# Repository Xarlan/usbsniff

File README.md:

# usbsniff
Develop hardware usb 2.0 sniffer

The main idea - to develop cheap hardware usb sniffer which possible to assemble at home :)

Current version based on MAX3421E

/pcb

This folder contain KiCad project of usb sniffer

## Limitation

Support follow EP:
* EP0: CONTROL (64 bytes)
* EP1: OUT, BULK or INTERRUPT
* EP2: IN, BULK or INTERRUPT
* EP3: IN, BULK or INTERRUPT

Thank you for "x8-999-github" for some good advices and idea.

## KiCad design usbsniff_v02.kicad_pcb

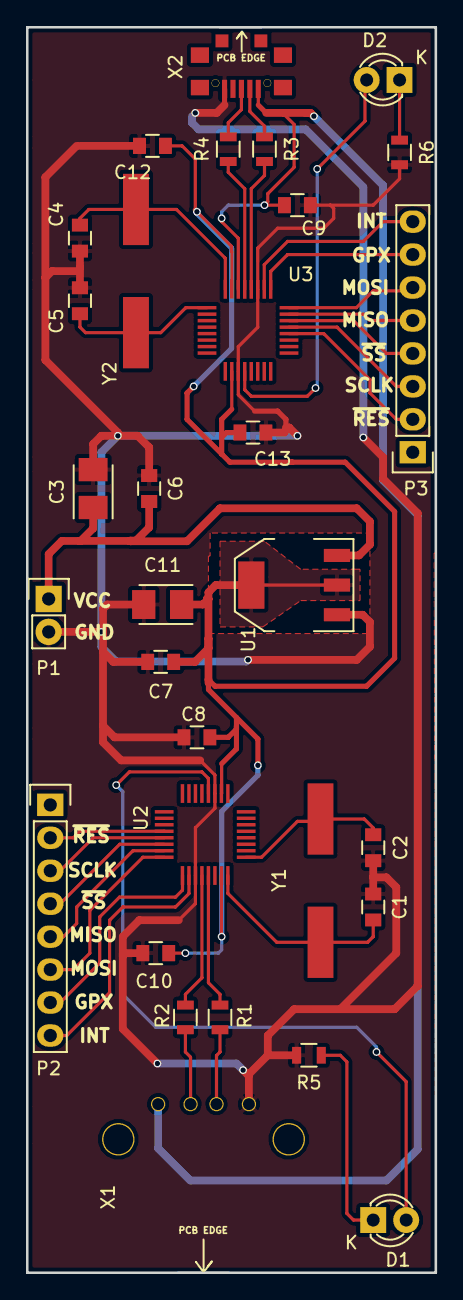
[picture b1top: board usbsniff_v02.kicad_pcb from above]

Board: 2 copper layers, 31.5 x 96.0 mm, 31 parts (0 on the bottom side), 34 nets.

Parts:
C1, C2, C4, C5: 20pF; C_0805
C3, C11: 10uF; TantalC_SizeB_EIA-3528_Reflow
C6, C7, C8, C13: 0.1uF; C_0805
C9, C10, C12: 1uF; C_0805
D1, D2: LED; LED-3MM
P1: CONN_01X02; Pin_Header_Straight_1x02
P2, P3: CONN_01X08; Pin_Header_Straight_1x08
R1, R2, R3, R4: 33 Ohm; R_0805
R5, R6: 470 Ohm; R_0805
U1: AMS1117; SOT-223
U2, U3: MAX3421E; TQFP-32_5x5mm
X1: USB_type_A; USBA_1J_DS_1095_WR
X2: micro_USB; micro_USB_KLS1-233-0-0-1-T
Y1, Y2: 12MHz; HC49-SM

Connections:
/RES_edevice: P3.2, U3.12
/RES_ehost: P2.2, U2.12
/Vcc_3.3V: C7.1, C8.1, C10.2, C11.1, C12.2, C13.1, U1.2, U1.4, U2.2, U2.23, U3.2, U3.23
/XI_device: C4.1, U3.24, Y2.1
/XI_host: C1.1, U2.24, Y1.1
/XO_device: C5.1, U3.25, Y2.2
/XO_host: C2.1, U2.25, Y1.2
/ed_VBCOMP: C9.1, U3.22, X1.1, X2.1
/edevice_DM: R3.2, U3.20
/edevice_DP: R4.2, U3.21
/ehost_DM: R2.1, U2.20
/ehost_DP: R1.1, U2.21
GND: C1.2, C2.2, C3.2, C4.2, C5.2, C6.2, C7.2, C8.2, C9.2, C10.1, C11.2, C12.1, C13.2, P1.2, R5.2, R6.2, U1.1, U2.3, U2.19, U3.3, U3.19, X1.4, X2.5
unnamed: C3.1, C6.1, P1.1, U1.3
unnamed: D1.1, R5.1
unnamed: D1.2, U2.4
unnamed: D2.1, R6.1
unnamed: D2.2, U3.4
unnamed: P2.3, U2.13
unnamed: P2.4, U2.14
unnamed: P2.5, U2.15
unnamed: P2.6, U2.16
unnamed: P2.7, U2.17
unnamed: P2.8, U2.18
unnamed: P3.3, U3.13
unnamed: P3.4, U3.14
unnamed: P3.5, U3.15
unnamed: P3.6, U3.16
unnamed: P3.7, U3.17
unnamed: P3.8, U3.18
unnamed: R1.2, X1.3
unnamed: R2.2, X1.2
unnamed: R3.1, X2.2
unnamed: R4.1, X2.3

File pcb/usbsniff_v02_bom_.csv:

Component,Description,Part,References,Value,Footprint,Quantity Per PCB,Datasheet
1,Unpolarized capacitor,C_Small,C6 C7 C8 C13,0.1uF,C_0805,4,
2,Polarised capacitor,CP_Small,C3 C11,10uF,TantalC_SizeB_EIA-3528_Reflow,2,
3,Unpolarized capacitor,C_Small,C9 C10 C12,1uF,C_0805,3,
4,Unpolarized capacitor,C_Small,C1 C2 C4 C5,20pF,C_0805,4,
5,,LED,D1 D2,LED,LED-3MM,2,
6,Connector 01x02,CONN_01X02,P1,CONN_01X02,Pin_Header_Straight_1x02,1,
7,Connector 01x08,CONN_01X08,P2 P3,CONN_01X08,Pin_Header_Straight_1x08,2,
8,Resistor,R_Small,R1 R2 R3 R4,33 Ohm,R_0805,4,
9,Resistor,R,R5 R6,470 Ohm,R_0805,2,
10,Adjustable/Fixed Low Dropout Linear Regulator,AMS1117,U1,AMS1117,SOT-223,1,
11,USB Peripheral/Host Controller with SPI Interface,MAX3421E,U2 U3,MAX3421E,TQFP-32_5x5mm,2,
12,"socket USB type A, horizontal placement",USB_type_A,X1,USB_type_A,USBA_1J_DS_1095_WR,1,
13,,micro_USB,X2,micro_USB,micro_USB_KLS1-233-0-0-1-T,1,
14,Two pin crystal,Crystal_Small,Y1 Y2,12MHz,HC49-SM,2,





Component Groups:,14
Component Count:,31
Fitted Components:,31
Number of PCBs:,1
Total components:,31
Schematic Version:,
Schematic Date:,
BoM Date:,Wed 21 Mar 2018 09:01:28 PM MSK
Schematic Source:,/home/xarlan/git/usbsniff/usbsniff_v02.sch
KiCad Version:,Eeschema 4.0.2+dfsg1-stable

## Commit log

2018-03-14 have done schematic and pcb based on MAX3421
2018-03-14 add picture of prototype
2018-03-21 add LED, redesign pcb
2018-03-22 redesign wires
2018-03-23 fix polygon around ams1117
2018-05-09 Create software
2018-05-09 Rename bom.ini to pcb/bom.ini
2018-05-09 Rename usbsniff_v02-cache.lib to pcb/usbsniff_v02-cache.lib
2018-05-09 Rename usbsniff_v02.bak to pcb/usbsniff_v02.bak
2018-05-09 Rename usbsniff_v02.kicad_pcb to pcb/usbsniff_v02.kicad_pcb
2018-05-09 Rename usbsniff_v02.kicad_pcb-bak to pcb/usbsniff_v02.kicad_pcb-bak
2018-05-09 Rename usbsniff_v02.net to pcb/usbsniff_v02.net
2018-05-09 Rename usbsniff_v02.pro to pcb/usbsniff_v02.pro
2018-05-09 Rename usbsniff_v02.sch to pcb/usbsniff_v02.sch
2018-05-09 Rename usbsniff_v02.xml to pcb/usbsniff_v02.xml
2018-05-09 Rename usbsniff_v02_add.net to pcb/usbsniff_v02_add.net
2018-05-09 Rename usbsniff_v02_bom_.csv to pcb/usbsniff_v02_bom_.csv
2018-05-09 Rename usbsniff_v02_max.net to pcb/usbsniff_v02_max.net
2018-05-09 Rename usbsniff_v03.net to pcb/usbsniff_v03.net
2018-05-09 add electric schema in pdf
2018-07-15 Rename software/usniff/main.c to software/usniff/main/main.c
2018-07-15 Rename software/usniff/max3421e.h to software/usniff/main/max3421e.h
2018-07-15 Rename software/usniff/usbconf.h to software/usniff/main/usbconf.h
2018-07-15 Update Makefile
2018-07-29 create test task BlinkLed to check pcb
2018-07-30 Update usbconf.h
    modified field in structure max3421e_msg.
    Add "reg", 'rw'
2018-07-30 Update main.c
    update "max3421e_rx_tx" function based on new format of struct max3421e_msg
2018-08-19 add spiMAX3421E.*
    void init_spi_Husb(spi_device_handle_t *hwnd_spi, spi_bus_config_t *buscfg, spi_device_interface_config_t *devcfg);
    void init_spi_Pusb(spi_device_handle_t *hwnd_spi, spi_bus_config_t *buscfg, spi_device_interface_config_t *devcfg);
    void w_reg(spi_device_handle_t hwnd_spi, uint8_t reg, uint8_t val);
    uint8_t r_reg(spi_device_handle_t hwnd_spi, uint8_t reg);
